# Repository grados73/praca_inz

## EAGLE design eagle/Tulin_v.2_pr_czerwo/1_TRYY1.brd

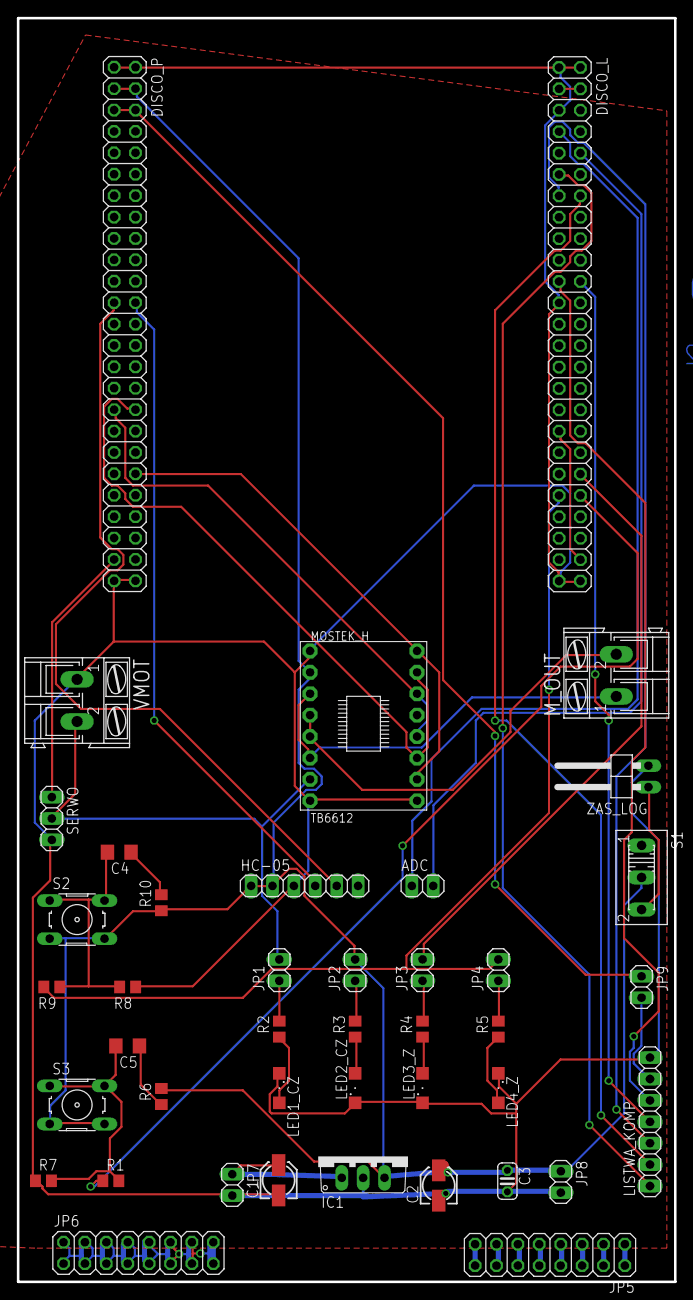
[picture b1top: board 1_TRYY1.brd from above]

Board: 2 copper layers, 78.0 x 150.0 mm, 42 parts (0 on the bottom side), 55 nets.

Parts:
ADC: 1X02
C1: 47uF; 153CLV-0405
C2: 470uF; 153CLV-0405
C3: 100nF; C025-024X044
C4, C5: 100n; C1206
DISCO_L: 2X25
DISCO_P: 2X25
HC-05: 1X06
IC1: 786TV; TO220V
JP1, JP2, JP3, JP4, JP7, JP8, JP9: 1X02
JP5, JP6: 2X08
LED1_CZ, LED2_CZ, LED3_Z, LED4_Z: SML1206
LISTWA_KOMP: 1X07
MOSTEK_H: MODUL_POLOLU
M_OUT: AK300/2
R1, R9: 330; R0805
R2: 300; R0805
R3: 150; R0805
R4, R5: 51; R0805
R6, R10: 100; R0805
R7, R8: 220k; R0805
S1: 255SB
S2, S3: B3F-10XX
SERWO: 1X03
VMOT: AK300/2
ZAS_LOG: 1X02/90

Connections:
3V: DISCO_P.5, DISCO_P.6, JP9.1
5V: C2.+, C3.1, DISCO_P.3, DISCO_P.4, HC-05.1, HC-05.2, IC1.3, JP2.2, JP8.1, MOSTEK_H.VCC, R6.2, R10.1, S1.2, S2.3, S2.4, S3.3, S3.4
A: JP9.2, LISTWA_KOMP.6
GND: C1.-, C2.-, C3.2, DISCO_L.1, DISCO_L.2, DISCO_L.5, DISCO_L.23, DISCO_L.49, DISCO_L.50, DISCO_P.1, DISCO_P.2, DISCO_P.49, DISCO_P.50, HC-05.3, IC1.2, JP7.2, JP8.2, LED1_CZ.C, LED2_CZ.C, LED3_Z.C, LED4_Z.C, LISTWA_KOMP.7, MOSTEK_H.GND1, MOSTEK_H.GND2, MOSTEK_H.GND3, R7.1, R8.1, SERWO.3, VMOT.1, ZAS_LOG.2
M_OUT_1: MOSTEK_H.AO1, MOSTEK_H.BO1, M_OUT.1
M_OUT_2: MOSTEK_H.A02, MOSTEK_H.BO2, M_OUT.2
unnamed: JP5.1, JP5.2
unnamed: JP5.3, JP5.4
unnamed: JP5.5, JP5.6
unnamed: JP5.7, JP5.8
unnamed: JP5.9, JP5.10
unnamed: JP5.11, JP5.12
unnamed: JP5.13, JP5.14
unnamed: JP5.15, JP5.16
unnamed: JP6.1, JP6.2
unnamed: JP6.3, JP6.4
unnamed: JP6.5, JP6.6
unnamed: JP6.7, JP6.8
unnamed: JP6.9, JP6.10
unnamed: JP6.11, JP6.12
unnamed: JP6.13, JP6.14
unnamed: JP6.15, JP6.16
unnamed: C1.+, IC1.1, JP7.1
unnamed: S1.3, ZAS_LOG.1
unnamed: LED1_CZ.A, R2.1
unnamed: LED2_CZ.A, R3.1
unnamed: C4.2, R8.2, R9.1, S2.1, S2.2
unnamed: JP1.1, R2.2
unnamed: C5.2, R1.2, R7.2, S3.1, S3.2
unnamed: JP2.1, R3.2
unnamed: LED3_Z.A, R4.1
unnamed: JP3.1, R4.2
unnamed: C4.1, R10.2
unnamed: C5.1, R6.1
unnamed: LED4_Z.A, R5.1
unnamed: JP4.1, R5.2
NC: DISCO_L.35, DISCO_L.48
PA1: DISCO_L.11, LISTWA_KOMP.1
PA2: DISCO_L.14, LISTWA_KOMP.2
PA3: DISCO_L.13, LISTWA_KOMP.3
PA15: DISCO_P.40, MOSTEK_H.PWMA, MOSTEK_H.PWMB
PB0: DISCO_L.22, LISTWA_KOMP.4
PB1: DISCO_L.21, LISTWA_KOMP.5
PB6: DISCO_P.23, HC-05.5
PB7: DISCO_P.24, HC-05.4
PC1: ADC.1, DISCO_L.7
PC2: ADC.2, DISCO_L.10
PC6: DISCO_P.47, SERWO.1
PD1: DISCO_P.33, MOSTEK_H.AIN1, MOSTEK_H.BIN1
PD2: DISCO_P.34, MOSTEK_H.AIN2, MOSTEK_H.BIN2
PD8: DISCO_L.40, JP3.2
PD9: DISCO_L.41, JP4.2, R9.2
PD10: DISCO_L.42, R1.1
VDD: DISCO_L.3, DISCO_L.4
VMOT: JP1.2, MOSTEK_H.VMOT, SERWO.2, VMOT.2
